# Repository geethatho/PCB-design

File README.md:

# PCB-design
pcb design of stm32 and pressure sensor

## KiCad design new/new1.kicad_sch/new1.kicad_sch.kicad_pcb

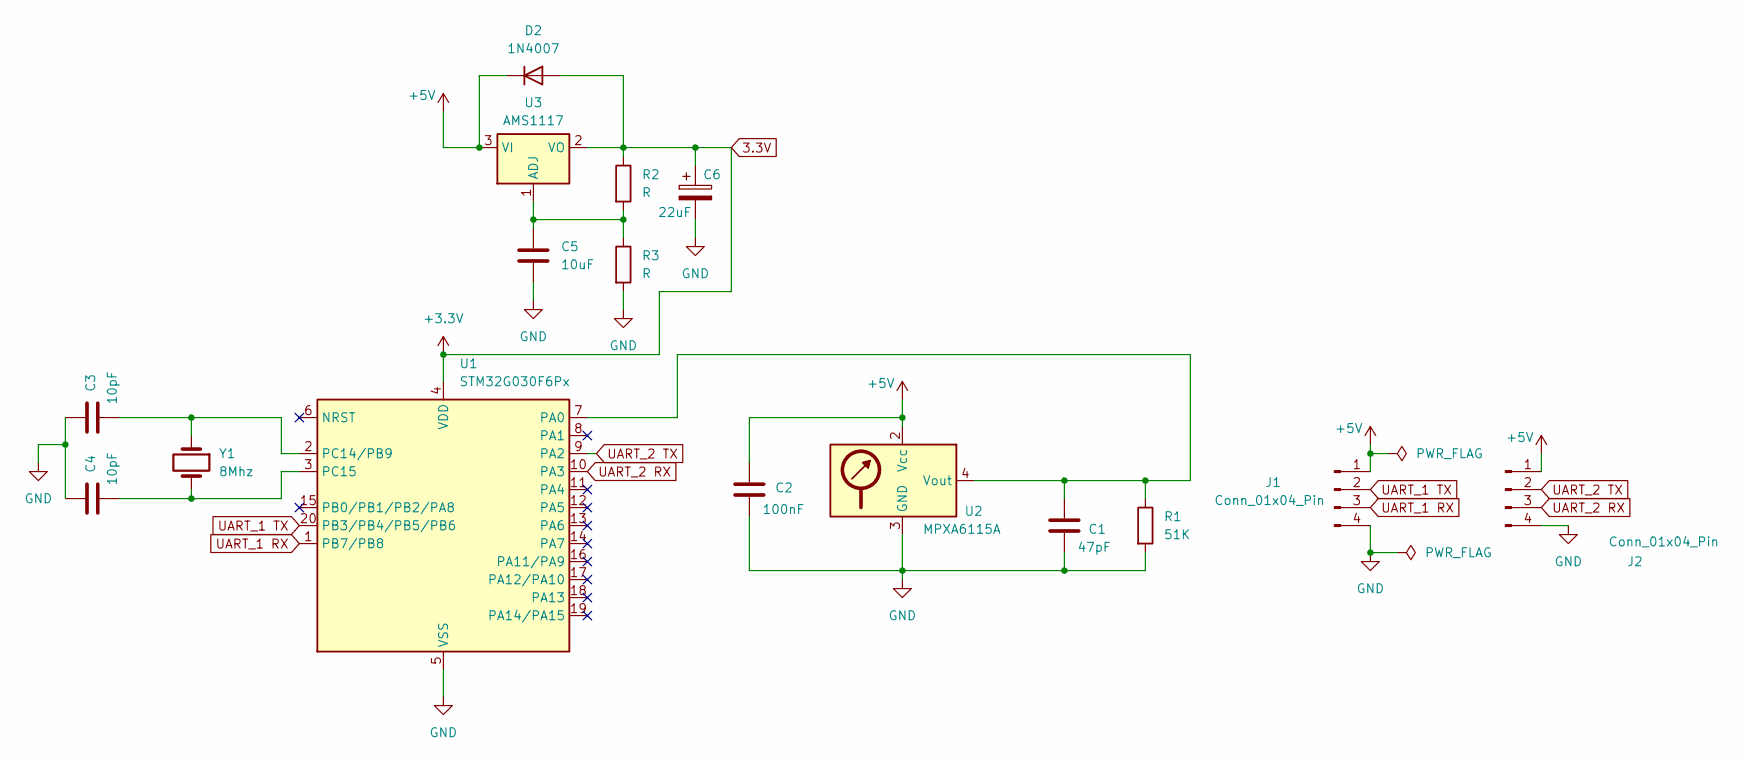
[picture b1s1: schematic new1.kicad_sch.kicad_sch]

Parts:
C1: 47pF; C_0603_1608Metric
C2: 100nF; C_0603_1608Metric
C3, C4: 10pF; C_0603_1608Metric
C5: 10uF; C_0603_1608Metric
C6: 22uF; C_0603_1608Metric
D2: 1N4007; D_DO-41_SOD81_P10.16mm_Horizontal
J1, J2: Conn_01x04_Pin; PinHeader_1x04_P2.54mm_Vertical
R1: 51K; R_0603_1608Metric
R2, R3: R; R_0603_1608Metric
U1: STM32G030F6Px; TSSOP-20_4.4x6.5mm_P0.65mm
U2: MPXA6115A; Freescale_98ARH99089A
U3: AMS1117; SOT-223-3_TabPin2
Y1: 8Mhz; Crystal_SMD_5032-2Pin_5.0x3.2mm

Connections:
3.3V: C6.1, D2.2 (A), R2.1, U1.4 (VDD), U3.2 (VO)
+5V: C2.1, D2.1 (K), J1.1, J2.1, U2.2 (Vcc), U3.3 (VI)
GND: C1.2, C2.2, C3.1, C4.1, C5.2, C6.2, J1.4, J2.4, R1.2, R3.2, U1.5 (VSS), U2.3 (GND)
unnamed: C1.1, R1.1, U1.7 (PA0), U2.4 (Vout)
unnamed: C3.2, U1.2 (PC14/PB9), Y1.1
unnamed: C4.2, U1.3 (PC15), Y1.2
unnamed: C5.1, R2.2, R3.1, U3.1 (ADJ)
UART_1 RX: J1.3, U1.1 (PB7/PB8)
UART_1 TX: J1.2, U1.20 (PB3/PB4/PB5/PB6)
UART_2 RX: J2.3, U1.10 (PA3)
UART_2 TX: J2.2, U1.9 (PA2)

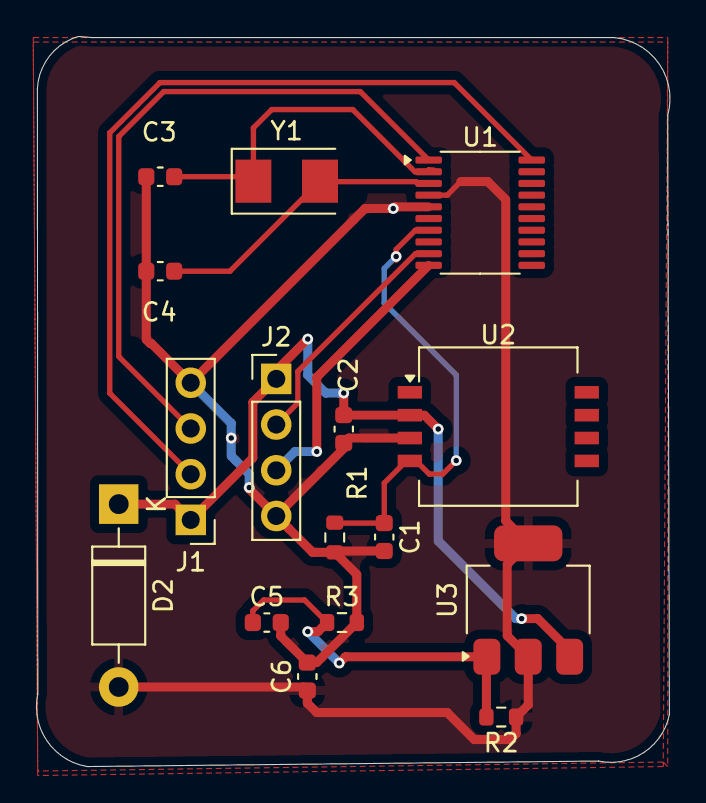
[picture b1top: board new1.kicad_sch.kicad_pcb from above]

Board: 2 copper layers, 35.2 x 40.6 mm, 16 parts (0 on the bottom side), 11 nets.

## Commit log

2024-07-30 updated n
2024-07-30 uodated
